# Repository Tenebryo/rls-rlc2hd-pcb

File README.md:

RLS RLC2HD PCB
==============

A simple PCB to mount a [RLS RLC2HD linear magnetic encoder](https://www.rls.si/eng/rlc2hd-miniature-linear-and-rotary-pcb-level-incremental-magnetic-encoder) and wire it to a pin header or compatible connector.

A pre-generated GERBER file is available in [/rls2hd-bob/output](/rls2hd-bob/output).

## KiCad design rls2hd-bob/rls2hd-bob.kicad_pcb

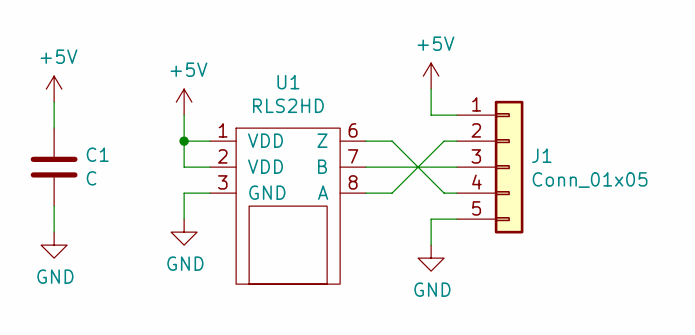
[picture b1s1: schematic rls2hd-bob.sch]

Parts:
C1: C; C_0805_2012Metric
J1: Conn_01x05; PinHeader_1x05_P2.54mm_Horizontal
U1: RLS2HD

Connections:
+5V: C1.1, J1.1, U1.1 (VDD), U1.2 (VDD)
GND: C1.2, J1.5, U1.3 (GND)
unnamed: J1.2, U1.8 (A)
unnamed: J1.3, U1.7 (B)
unnamed: J1.4, U1.6 (Z)

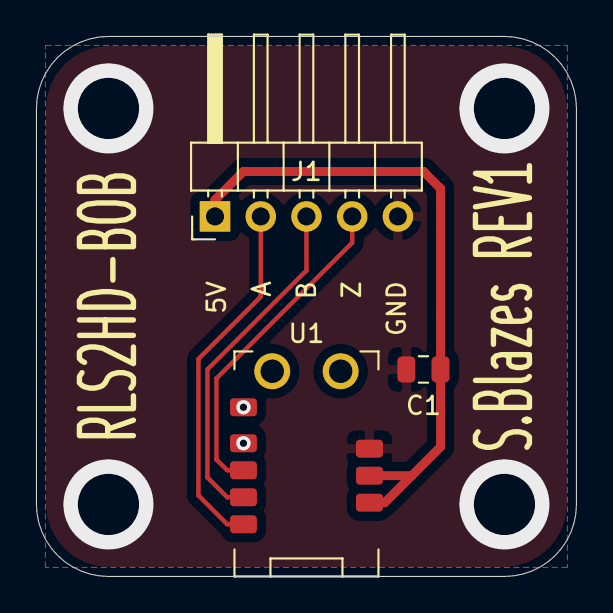
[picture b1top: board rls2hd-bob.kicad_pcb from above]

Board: 2 copper layers, 30.0 x 30.0 mm, 3 parts (0 on the bottom side), 5 nets.
